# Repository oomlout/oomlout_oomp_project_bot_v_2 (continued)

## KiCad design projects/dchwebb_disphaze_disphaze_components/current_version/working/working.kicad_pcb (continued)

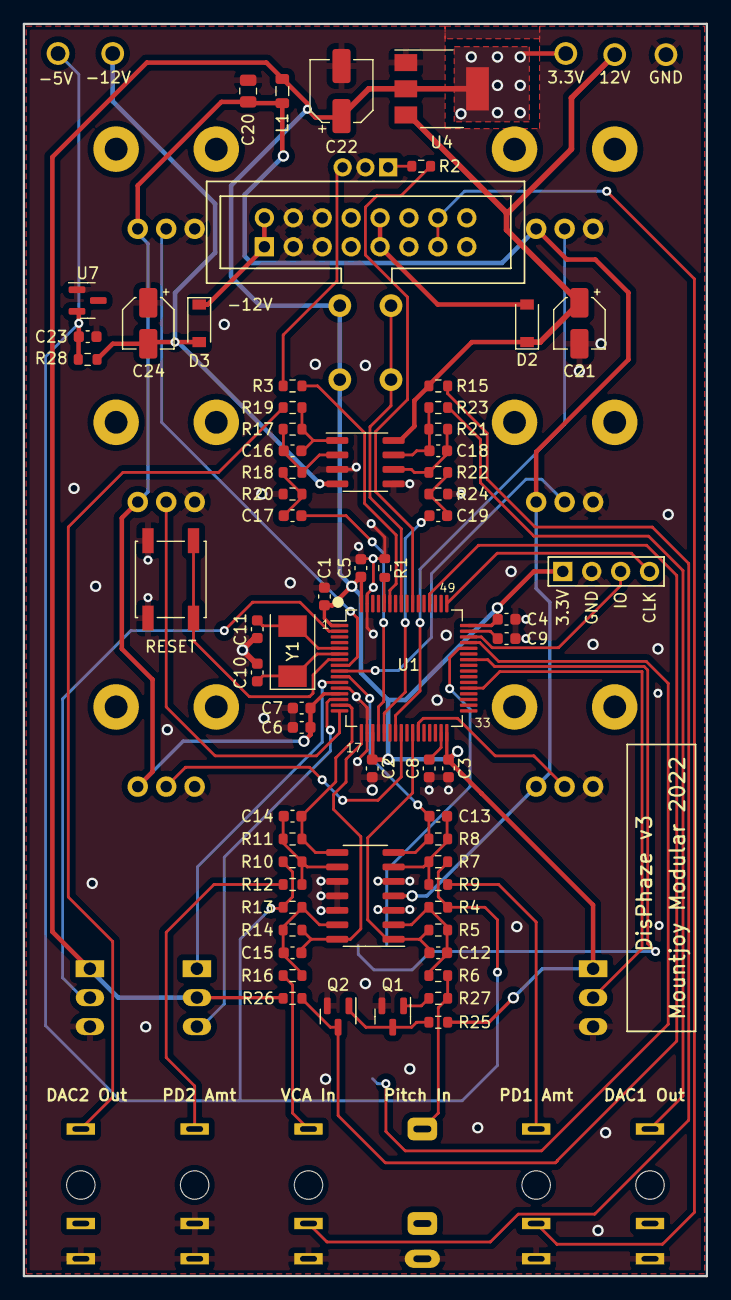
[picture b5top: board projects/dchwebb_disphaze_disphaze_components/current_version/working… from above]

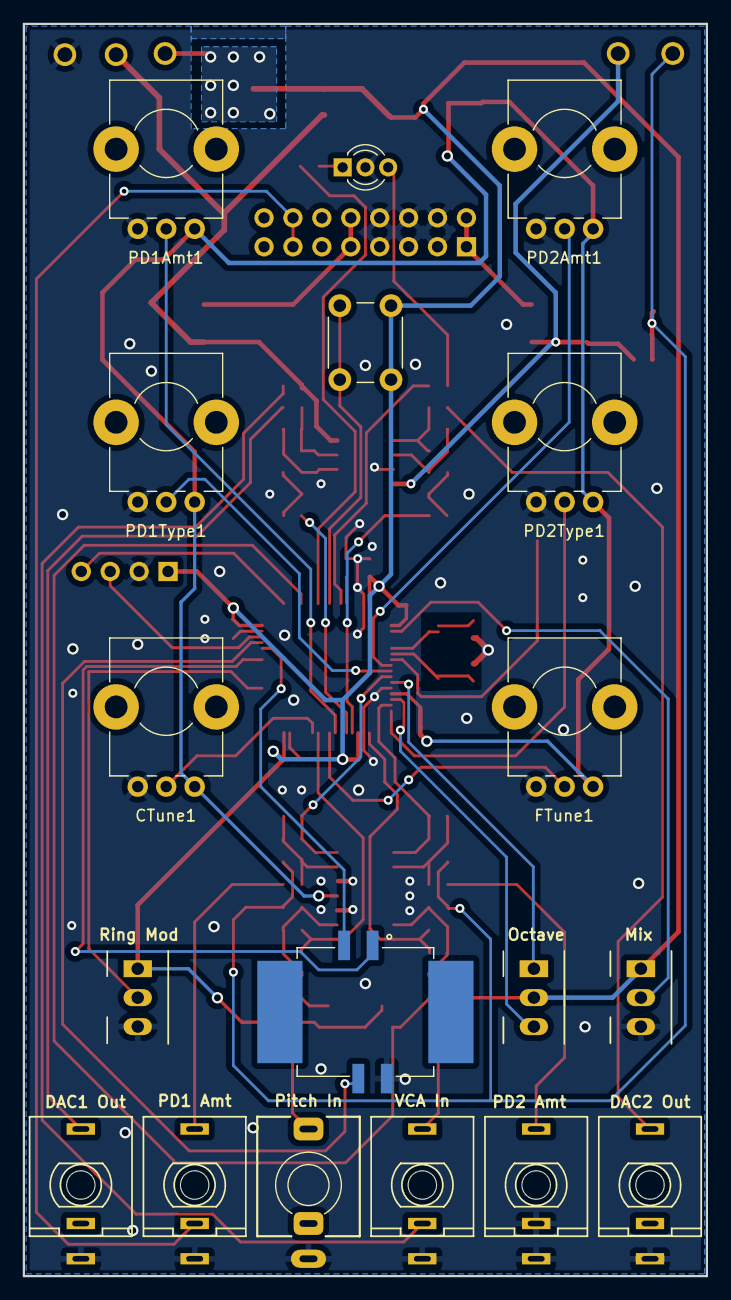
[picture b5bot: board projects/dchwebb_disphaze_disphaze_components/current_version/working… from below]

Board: 2 copper layers, 60.0 x 110.0 mm, 89 parts (18 on the bottom side), 61 nets.

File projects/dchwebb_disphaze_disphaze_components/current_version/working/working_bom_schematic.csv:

"Source:","C:\gh\oomlout_oomp_project_bot_v_2\projects\dchwebb_disphaze_disphaze_components\current_version\working\working.kicad_sch"
"Date:","30/09/2023 03:19:28"
"Tool:","Eeschema 7.0.6"
"Generator:","C:/Program Files/KiCad/7.0/bin/scripting/plugins/bom_csv_grouped_by_value_with_fp.py"
"Component Count:","89"
"Ref","Qnty","Value","Cmp name","Footprint","Description","Vendor","DNP"
"C1","1","4.7uF","C_Small","Capacitor_SMD:C_0603_1608Metric","Unpolarized capacitor, small symbol","",""
"C2, C3, C4, C5, C7, C23","6","100nF","C_Small","Capacitor_SMD:C_0603_1608Metric","Unpolarized capacitor, small symbol","",""
"C6","1","1uF","C_Small","Capacitor_SMD:C_0603_1608Metric","Unpolarized capacitor, small symbol","",""
"C8, C9","2","2.2uF","C_Small","Capacitor_SMD:C_0603_1608Metric","Unpolarized capacitor, small symbol","",""
"C10, C11","2","30pF","C_Small","Capacitor_SMD:C_0603_1608Metric","Unpolarized capacitor, small symbol","",""
"C12, C14","2","2.2nF","C_Small","Capacitor_SMD:C_0603_1608Metric","Unpolarized capacitor, small symbol","",""
"C13, C15","2","1.5nF","C_Small","Capacitor_SMD:C_0603_1608Metric","Unpolarized capacitor, small symbol","",""
"C16, C18","2","22pF","C_Small","Capacitor_SMD:C_0603_1608Metric","Unpolarized capacitor, small symbol","",""
"C17, C19","2","10uF","C_Small","Capacitor_SMD:C_0603_1608Metric","Unpolarized capacitor, small symbol","",""
"C20","1","10uF","C_Small","Capacitor_SMD:C_0805_2012Metric","Unpolarized capacitor, small symbol","",""
"C21, C24","2","22uF","C_Polarized_Small","Capacitor_SMD:CP_Elec_4x5.3","Polarized capacitor, small symbol","",""
"C22","1","47uF","C_Polarized_Small","Capacitor_SMD:CP_Elec_5x5.4","Polarized capacitor, small symbol","",""
"CTune1","1","B10k","R_Potentiometer","Custom_Footprints:Alpha_9mm_Potentiometer_Aligned","Potentiometer","",""
"D1","1","LED_Dual_AKA","LED_Dual_AKA","LED_THT:LED_D3.0mm-3","Dual LED, common cathode on pin 2","",""
"D2, D3","2","1N5819","1N5819","Diode_SMD:D_SOD-123","40V 1A Schottky Barrier Rectifier Diode, DO-41","",""
"FTune1","1","B10k","R_Potentiometer","Custom_Footprints:Alpha_9mm_Potentiometer_Aligned","Potentiometer","",""
"J1","1","SWD_Header","Conn_01x04_Male","Custom_Footprints:SWD_header","Generic connector, single row, 01x04, script generated (kicad-library-utils/schlib/autogen/connector/)","",""
"J2","1","USB_B_Micro","1734517-1","Custom_Footprints:USB_TE_1734517-1","","",""
"J3","1","PItch_In","AudioJack3","Custom_Footprints:Thonkiconn_Stereo-PJ366ST","Audio Jack, 3 Poles (Stereo / TRS)","",""
"J4","1","PD1_Amt_In","AudioJack2_Ground_Switch","Custom_Footprints:THONKICONN_hole","Audio Jack, 2 Poles (Mono / TS), Switched Pole (Normalling)","",""
"J5","1","PD2_Amt_In","AudioJack2_Ground_Switch","Custom_Footprints:THONKICONN_hole","Audio Jack, 2 Poles (Mono / TS), Switched Pole (Normalling)","",""
"J6","1","VCA_In","AudioJack2_Ground_Switch","Custom_Footprints:THONKICONN_hole","Audio Jack, 2 Poles (Mono / TS), Switched Pole (Normalling)","",""
"J7","1","DAC1_Out","AudioJack2_Ground_Switch","Custom_Footprints:THONKICONN_hole","Audio Jack, 2 Poles (Mono / TS), Switched Pole (Normalling)","",""
"J8","1","DAC2_Out","AudioJack2_Ground_Switch","Custom_Footprints:THONKICONN_hole","Audio Jack, 2 Poles (Mono / TS), Switched Pole (Normalling)","",""
"J9","1","Eurorack_16_pin_power","Eurorack_16_pin_power","Custom_Footprints:Eurorack_16_pin_header","","",""
"L1","1","L","L","Inductor_SMD:L_0805_2012Metric","Inductor","",""
"PD1Amt1","1","B10k","R_Potentiometer","Custom_Footprints:Alpha_9mm_Potentiometer_Aligned","Potentiometer","",""
"PD1Type1","1","B10k","R_Potentiometer","Custom_Footprints:Alpha_9mm_Potentiometer_Aligned","Potentiometer","",""
"PD2Amt1","1","B10k","R_Potentiometer","Custom_Footprints:Alpha_9mm_Potentiometer_Aligned","Potentiometer","",""
"PD2Type1","1","B10k","R_Potentiometer","Custom_Footprints:Alpha_9mm_Potentiometer_Aligned","Potentiometer","",""
"Q1, Q2","2","MMBT3904","MMBT3904","Package_TO_SOT_SMD:SOT-23","0.2A Ic, 40V Vce, Small Signal NPN Transistor, SOT-23","",""
"R1, R6, R9, R12, R16","5","100k","R_Small","Resistor_SMD:R_0603_1608Metric","Resistor, small symbol","",""
"R2, R3, R19, R23","4","1k","R_Small","Resistor_SMD:R_0603_1608Metric","Resistor, small symbol","",""
"R4","1","91k","R_Small","Resistor_SMD:R_0603_1608Metric","Resistor, small symbol","",""
"R5","1","56k","R_Small","Resistor_SMD:R_0603_1608Metric","Resistor, small symbol","",""
"R7","1","82k","R_Small","Resistor_SMD:R_0603_1608Metric","Resistor, small symbol","",""
"R8, R11, R14, R15, R20, R24","6","47k","R_Small","Resistor_SMD:R_0603_1608Metric","Resistor, small symbol","",""
"R10, R13, R17, R21","4","68k","R_Small","Resistor_SMD:R_0603_1608Metric","Resistor, small symbol","",""
"R18, R22","2","6.8k","R_Small","Resistor_SMD:R_0603_1608Metric","Resistor, small symbol","",""
"R25, R26, R27","3","4k7","R_Small","Resistor_SMD:R_0603_1608Metric","Resistor, small symbol","",""
"R28","1","2.2k","R_Small","Resistor_SMD:R_0603_1608Metric","Resistor, small symbol","",""
"RESET1","1","SW_Push","SW_Push","Custom_Footprints:SW_SPST_EVQQ2","Push button switch, generic, two pins","",""
"SW1","1","Octave_Switch","SW_SPDT_MSM","Custom_Footprints:SPDTSubMiniature","Switch, single pole double throw, center OFF position","",""
"SW2","1","DAC1_RingMod_Switch","SW_SPDT","Custom_Footprints:SPDTSubMiniature","Switch, single pole double throw","",""
"SW3","1","DAC2_Mix_Switch","SW_SPDT","Custom_Footprints:SPDTSubMiniature","Switch, single pole double throw","",""
"SW4","1","SW_Push","SW_Push","Custom_Footprints:SW_PUSH_6mm_aligned","Push button switch, generic, two pins","",""
"TP1, TP2, TP3, TP4, TP5","5","TestPoint","TestPoint","Custom_Footprints:1.3mm_Test_Point","test point","",""
"U1","1","STM32F405RGTx","STM32F405RGTx","Package_QFP:LQFP-64_10x10mm_P0.5mm","ARM Cortex-M4 MCU, 1024KB flash, 128KB RAM, 168MHz, 1.8-3.6V, 51 GPIO, LQFP-64","",""
"U2","1","TL072","TL072","Package_SO:SOIC-8_3.9x4.9mm_P1.27mm","Dual Low-Noise JFET-Input Operational Amplifiers, DIP-8/SOIC-8","",""
"U3","1","MCP6004","MCP6004","Package_SO:SOIC-14_3.9x8.7mm_P1.27mm","1MHz, Low-Power Op Amp, DIP-14/SOIC-14/TSSOP-14","",""
"U4","1","LM1117-3.3","LM1117-3.3","Package_TO_SOT_SMD:SOT-223-3_TabPin2","800mA Low-Dropout Linear Regulator, 3.3V fixed output, TO-220/TO-252/TO-263/SOT-223","",""
"U7","1","LM4040DBZ-5","LM4040DBZ-5","Package_TO_SOT_SMD:SOT-23","5.000V Precision Micropower Shunt Voltage Reference, SOT-23","",""
"Y1","1","12MHz_18pF","Crystal_Small","Crystal:Crystal_SMD_0603-2Pin_6.0x3.5mm","Two pin crystal, small symbol","",""

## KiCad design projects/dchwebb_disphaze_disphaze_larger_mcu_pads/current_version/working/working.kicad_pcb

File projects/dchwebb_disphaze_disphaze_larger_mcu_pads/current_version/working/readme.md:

# disphaze
 
## summary 
* id: dchwebb_disphaze_disphaze_larger_mcu_pads
* user: dchwebb
* name: disphaze
* board: disphaze_larger_mcu_pads
* repo: https://github.com/dchwebb/DisPhaze
* src_file_repo_kicad_pcb: Hardware/DisPhaze.kicad_pcb
* src_file_repo_kicad_pcb_link: https://github.com/dchwebb/DisPhaze/tree/master/Hardware/DisPhaze.kicad_pcb
* src_file_repo_kicad_sch: Hardware/DisPhaze.kicad_sch
* src_file_repo_kicad_sch_link: https://github.com/dchwebb/DisPhaze/tree/master/Hardware/DisPhaze.kicad_sch

* src_file_repo_sch: Hardware/DisPhaze.sch
* src_file_repo_sch_link: https://github.com/dchwebb/DisPhaze/tree/master/Hardware/DisPhaze.sch
* full details link: https://github.com/oomlout/oomlout_oomp_project_bot_v_2/tree/main/projects/dchwebb_disphaze_disphaze_larger_mcu_pads/current_version/working

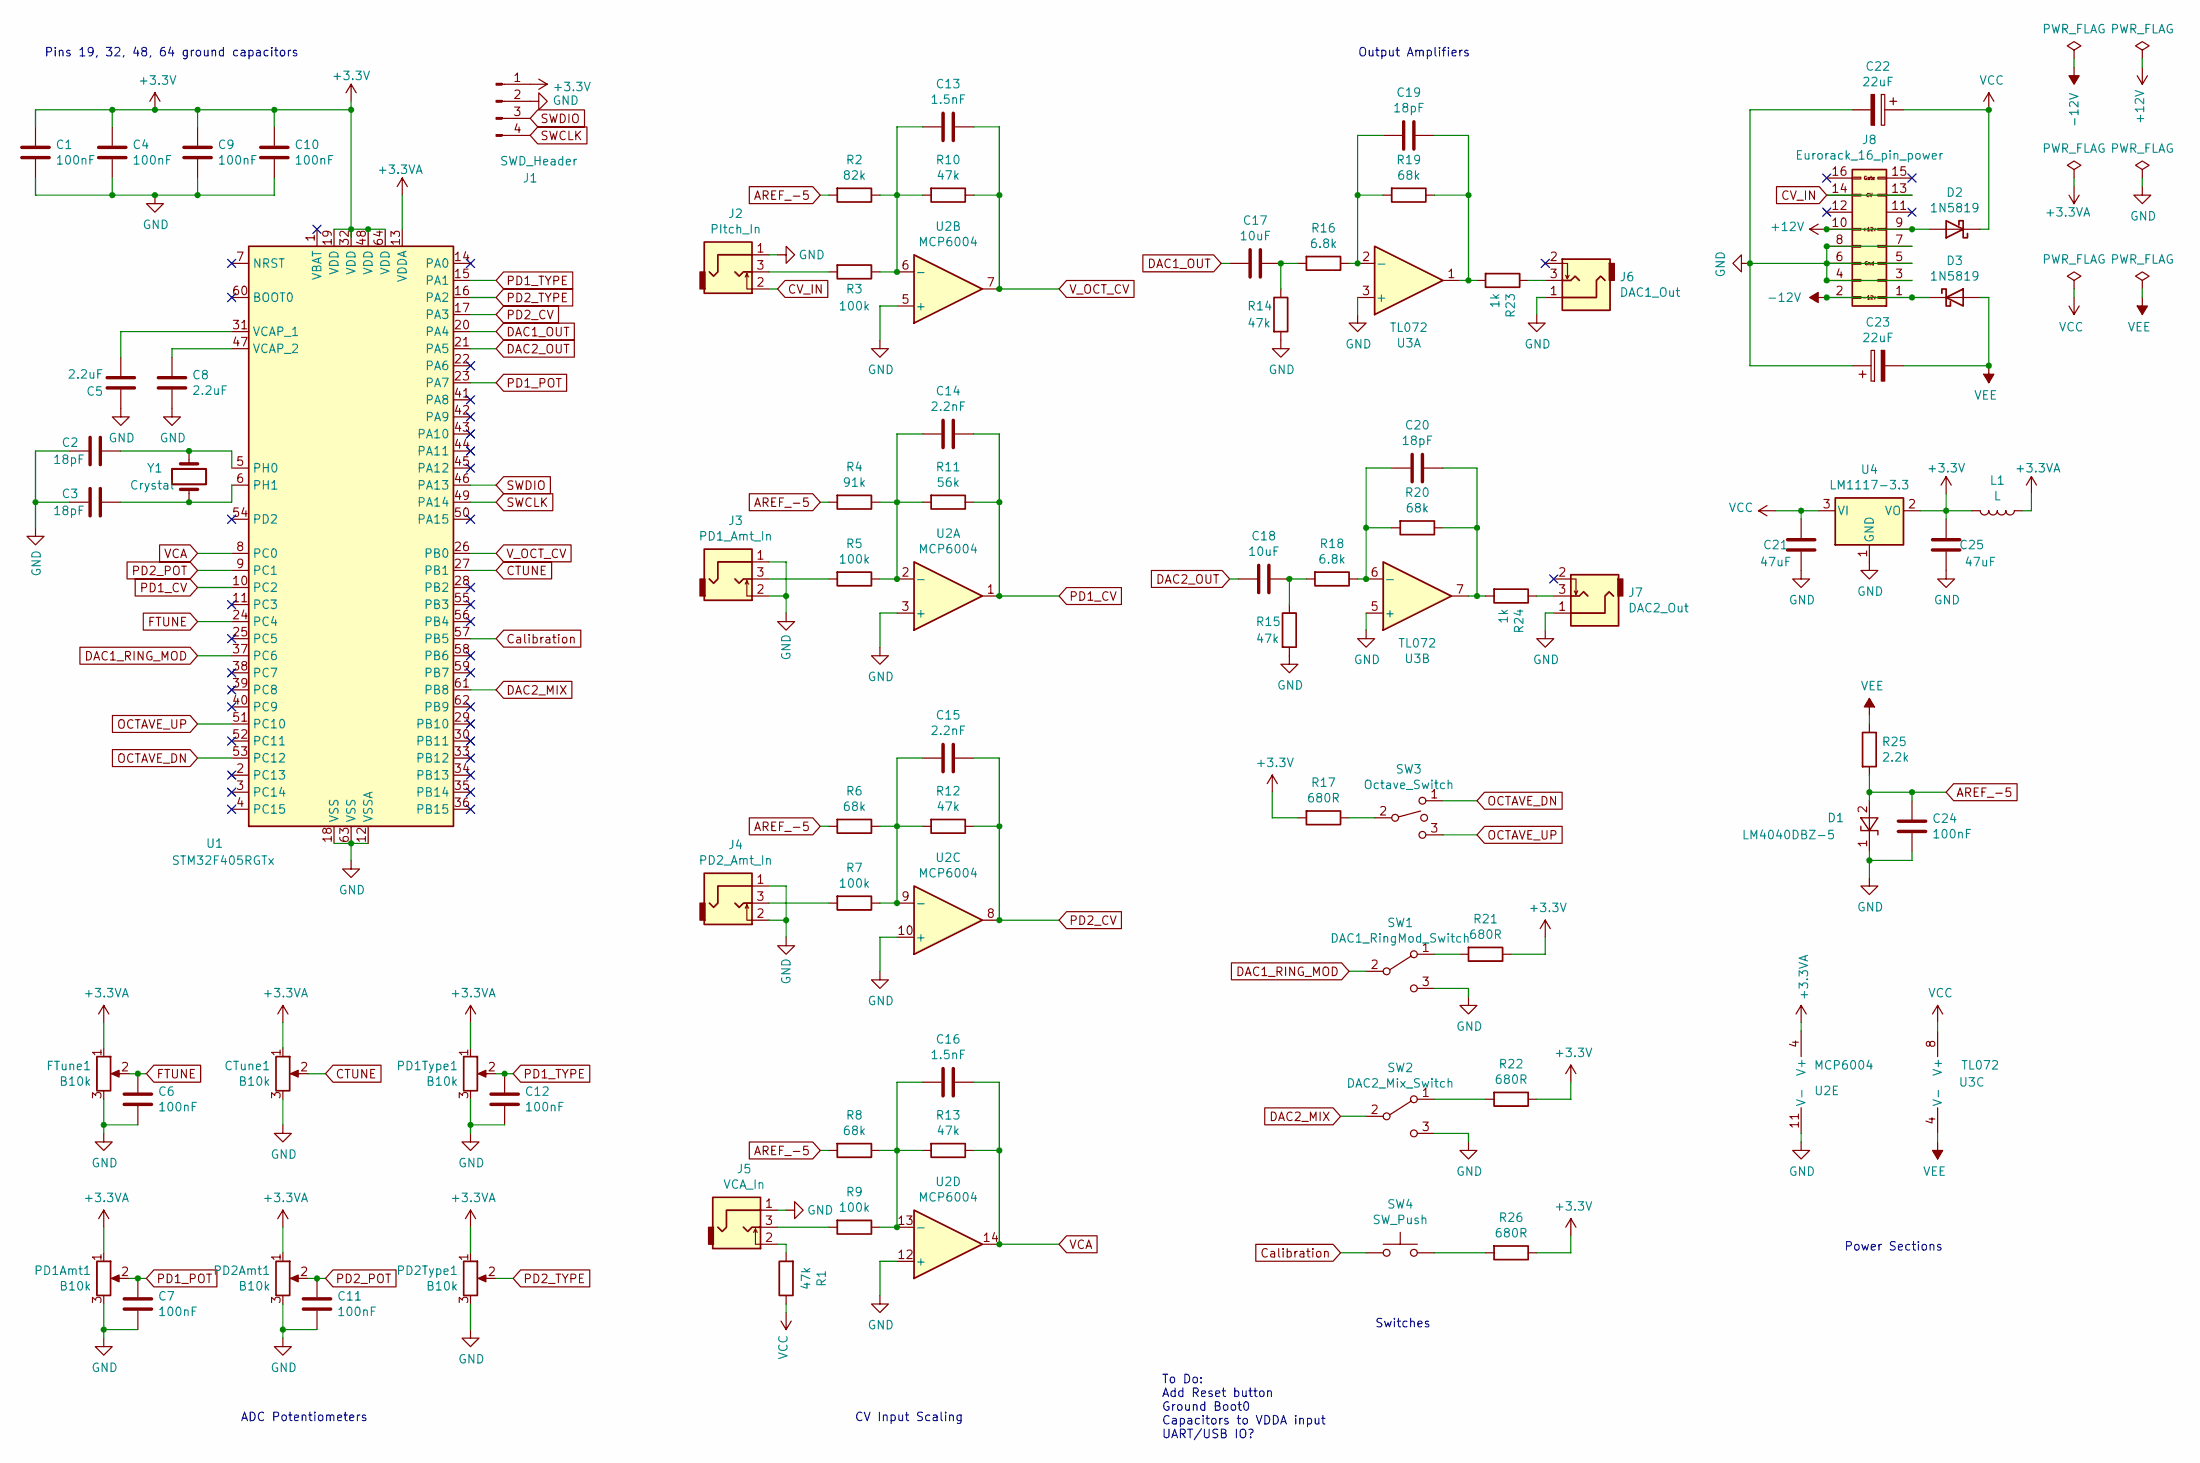
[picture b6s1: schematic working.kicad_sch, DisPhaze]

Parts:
C1, C4, C6, C7, C9, C10, C11, C12, C24: 100nF; C_0805_HandSoldering
C2, C3, C19, C20: 18pF; C_0805_HandSoldering
C5, C8: 2.2uF; C_0805_HandSoldering
C13, C16: 1.5nF; C_0805_HandSoldering
C14, C15: 2.2nF; C_0805_HandSoldering
C17, C18: 10uF; C_0805_HandSoldering
C21, C25: 47uF; CP_Elec_5x5.8
C22, C23: 22uF; CP_Elec_4x5.8
CTune1: B10k; Alpha_9mm_Potentiometer
D1: LM4040DBZ-5; SOT-23
D2, D3: 1N5819; D_SOD-123
FTune1: B10k; Alpha_9mm_Potentiometer
J1: SWD_Header; SWD_header
J2: PItch_In; THONKICONN_hole
J3: PD1_Amt_In; THONKICONN_hole
J4: PD2_Amt_In; THONKICONN_hole
J5: VCA_In; THONKICONN_hole
J6: DAC1_Out; THONKICONN_hole
J7: DAC2_Out; THONKICONN_hole
J8: Eurorack_16_pin_power; Eurorack_16_pin_header
L1: L; R_0805_HandSoldering
PD1Amt1, PD1Type1, PD2Amt1, PD2Type1: B10k; Alpha_9mm_Potentiometer
R1, R10, R12, R13, R14, R15: 47k; R_0805_HandSoldering
R2: 82k; R_0805_HandSoldering
R3, R5, R7, R9: 100k; R_0805_HandSoldering
R4: 91k; R_0805_HandSoldering
R6, R8, R19, R20: 68k; R_0805_HandSoldering
R11: 56k; R_0805_HandSoldering
R16, R18: 6.8k; R_0805_HandSoldering
R17, R21, R22, R26: 680R; R_0805_HandSoldering
R23, R24: 1k; R_0805_HandSoldering
R25: 2.2k; R_0805_HandSoldering
SW1: DAC1_RingMod_Switch; SPDTSubMiniature
SW2: DAC2_Mix_Switch; SPDTSubMiniature
SW3: Octave_Switch; SPDTSubMiniature
SW4: SW_Push; SW_SPST_EVQQ2
U1: STM32F405RGTx; LQFP-64_10x10mm_P0.5mm
U2: MCP6004; SOIC-14_N
U3: TL072; SOIC-8-N
U4: LM1117-3.3; TO-252-3_TabPin2
Y1: Crystal; Crystal_SMD

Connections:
+3.3VA: CTune1.1, FTune1.1, L1.1, PD1Amt1.1, PD1Type1.1, PD2Amt1.1, PD2Type1.1, U1.13 (VDDA), U2.4 (V+)
+3V3: C1.1, C4.1, C9.1, C10.1, C25.1, J1.1, L1.2, R17.2, R21.1, R22.1, R26.1, U1.19 (VDD), U1.32 (VDD), U1.48 (VDD), U1.64 (VDD), U4.2 (VO)
+12V: D2.2 (A), J8.9, J8.10
-12V: D3.1 (K), J8.1, J8.2
AREF_-5: C24.1, D1.2 (A), R2.2, R4.2, R6.2, R8.2, R25.2
CTUNE: CTune1.2, U1.27 (PB1)
CV_IN: J2.2, J8.13, J8.14
Calibration: SW4.1, U1.57 (PB5)
DAC1_OUT: C17.2, U1.20 (PA4)
DAC1_RING_MOD: SW1.2 (B), U1.37 (PC6); also elsewhere on the board
DAC2_MIX: SW2.2 (B), U1.61 (PB8)
DAC2_OUT: C18.2, U1.21 (PA5)
FTUNE: C6.1, FTune1.2, U1.24 (PC4)
GND: C1.2, C2.2, C3.2, C4.2, C5.1, C6.2, C7.2, C8.2, C9.2, C10.2, C11.2, C12.2, C21.2, C22.2, C23.1, C24.2, C25.2, CTune1.3, D1.1 (K), FTune1.3, J1.2, J2.1, J3.1, J3.2, J4.1, J4.2, J5.1, J6.1, J7.1, J8.3, J8.4, J8.5, J8.6, J8.7, J8.8, PD1Amt1.3, PD1Type1.3, PD2Amt1.3, PD2Type1.3, R14.2, R15.2, SW1.3 (C), SW2.3 (C), U1.12 (VSSA), U1.18 (VSS), U1.63 (VSS), U2.3 (+), U2.5 (+), U2.10 (+), U2.11 (V-), U2.12 (+), U3.3 (+), U3.5 (+), U4.1 (GND); also elsewhere on the board
unnamed: C2.1, U1.5 (PH0), Y1.2
unnamed: C3.1, U1.6 (PH1), Y1.1
unnamed: C5.2, U1.31 (VCAP_1)
unnamed: C8.1, U1.47 (VCAP_2)
unnamed: C13.1, R2.1, R3.1, R10.2, U2.6 (-)
unnamed: C14.1, R4.1, R5.1, R11.2, U2.2 (-)
unnamed: C15.1, R6.1, R7.1, R12.2, U2.9 (-)
unnamed: C16.1, R8.1, R9.1, R13.2, U2.13 (-)
unnamed: C17.1, R14.1, R16.2
unnamed: C18.1, R15.1, R18.2
unnamed: C19.1, R16.1, R19.2, U3.2 (-)
unnamed: C19.2, R19.1, R23.2, U3.1
unnamed: C20.1, R18.1, R20.2, U3.6 (-)
unnamed: C20.2, R20.1, R24.2, U3.7
unnamed: J2.3, R3.2
unnamed: J3.3, R5.2
unnamed: J4.3, R7.2
unnamed: J5.2, R1.2
unnamed: J5.3, R9.2
unnamed: J6.3, R23.1
unnamed: J7.3, R24.1
unnamed: R17.1, SW3.2
unnamed 42: R21.2, SW1.1 (A); also elsewhere on the board
unnamed: R22.2, SW2.1 (A)
unnamed: R26.2, SW4.2
OCTAVE_DN: SW3.1, U1.53 (PC12)
OCTAVE_UP: SW3.3, U1.51 (PC10)
PD1_CV: C14.2, R11.1, U1.10 (PC2), U2.1
PD1_POT: C7.1, PD1Amt1.2, U1.23 (PA7)
PD1_TYPE: C12.1, PD1Type1.2, U1.15 (PA1)
PD2_CV: C15.2, R12.1, U1.17 (PA3), U2.8
PD2_POT: C11.1, PD2Amt1.2, U1.9 (PC1)
PD2_TYPE: PD2Type1.2, U1.16 (PA2)
SWCLK: J1.4, U1.49 (PA14)
SWDIO: J1.3, U1.46 (PA13)
VCA: C16.2, R13.1, U1.8 (PC0), U2.14
VCC: C21.1, C22.1, D2.1 (K), R1.1, U3.8 (V+), U4.3 (VI)
VEE: C23.2, D3.2 (A), R25.1, U3.4 (V-)
V_OCT_CV: C13.2, R10.1, U1.26 (PB0), U2.7

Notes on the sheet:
To Do: Add Reset button Ground Boot0 Capacitors to VDDA input UART/USB IO?
Output Amplifiers
Switches
Pins 19, 32, 48, 64 ground capacitors
Power Sections
ADC Potentiometers
CV Input Scaling

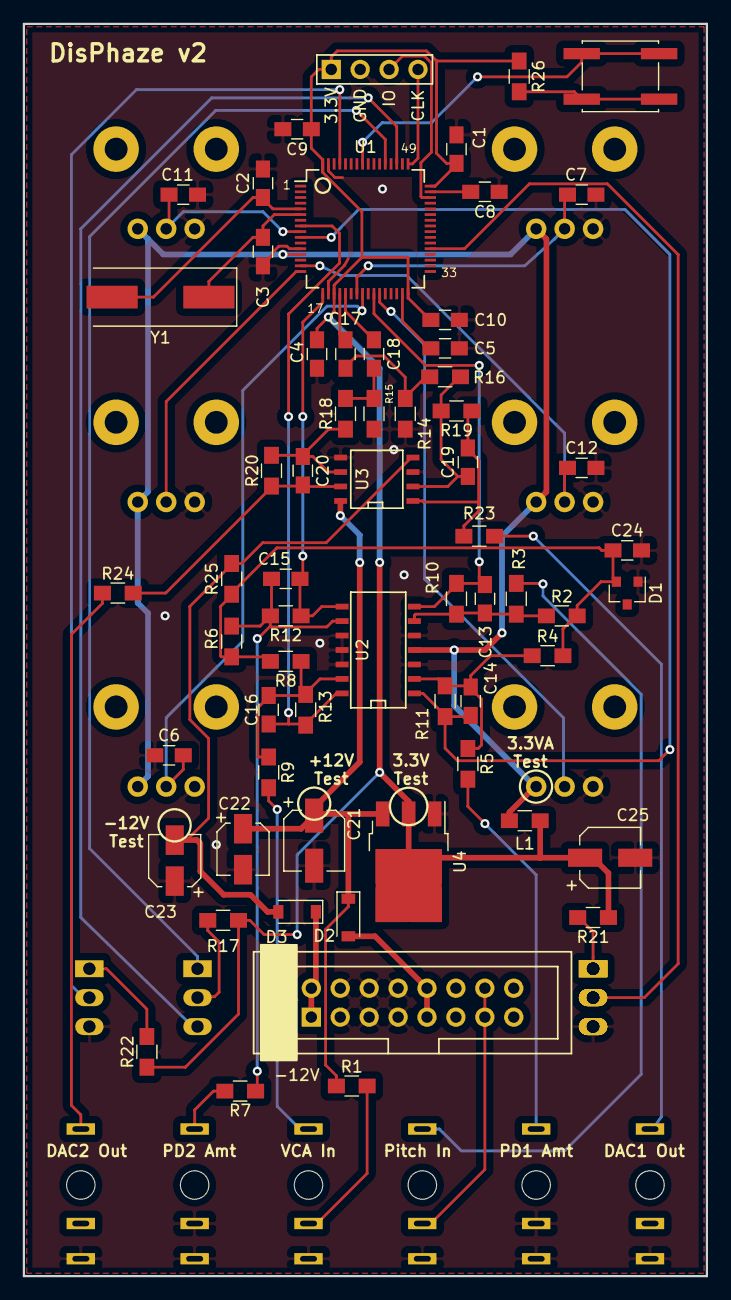
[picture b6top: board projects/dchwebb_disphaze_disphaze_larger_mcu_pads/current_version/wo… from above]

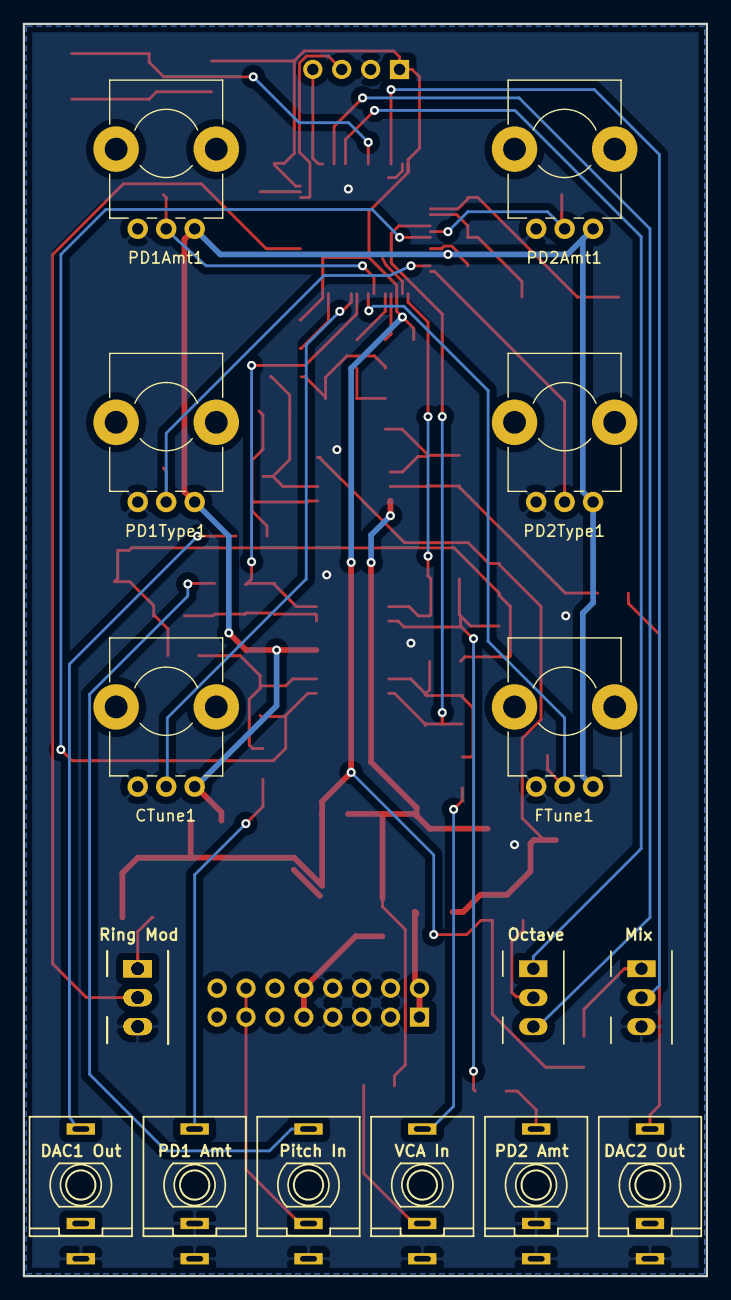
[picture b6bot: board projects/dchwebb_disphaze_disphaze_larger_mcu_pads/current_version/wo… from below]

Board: 2 copper layers, 60.0 x 110.0 mm, 80 parts (17 on the bottom side), 53 nets.

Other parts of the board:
SW1#2, SW1#3: DAC1_RingMod_Switch; SPDTSubMiniature

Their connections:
DAC1_RING_MOD: SW1#2.2, SW1#3.2; also elsewhere on the board
GND: SW1#2.3, SW1#3.3; also elsewhere on the board
unnamed 42: SW1#2.1, SW1#3.1; also elsewhere on the board

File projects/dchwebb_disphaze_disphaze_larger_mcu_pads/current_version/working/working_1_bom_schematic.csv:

"Source:","C:\gh\oomlout_oomp_project_bot_v_2\projects\dchwebb_disphaze_disphaze_larger_mcu_pads\current_version\working\working_1.kicad_sch"
"Date:","30/09/2023 03:29:46"
"Tool:","Eeschema 7.0.6"
"Generator:","C:/Program Files/KiCad/7.0/bin/scripting/plugins/bom_csv_grouped_by_value_with_fp.py"
"Component Count:","78"
"Ref","Qnty","Value","Cmp name","Footprint","Description","Vendor","DNP"
"C1, C4, C6, C7, C9, C10, C11, C12, C24","9","100nF","C","Capacitors_SMD:C_0805_HandSoldering","Unpolarized capacitor","",""
"C2, C3, C19, C20","4","18pF","C","Capacitors_SMD:C_0805_HandSoldering","Unpolarized capacitor","",""
"C5, C8","2","2.2uF","C","Capacitors_SMD:C_0805_HandSoldering","Unpolarized capacitor","",""
"C13, C16","2","1.5nF","C","Capacitors_SMD:C_0805_HandSoldering","Unpolarized capacitor","",""
"C14, C15","2","2.2nF","C","Capacitors_SMD:C_0805_HandSoldering","Unpolarized capacitor","",""
"C17, C18","2","10uF","C","Capacitors_SMD:C_0805_HandSoldering","Unpolarized capacitor","",""
"C21, C25","2","47uF","C","Capacitors_SMD:CP_Elec_5x5.8","Unpolarized capacitor","",""
"C22, C23","2","22uF","CP","Capacitors_SMD:CP_Elec_4x5.8","","",""
"CTune1","1","B10k","R_POT","Custom_Footprints:Alpha_9mm_Potentiometer","","",""
"D1","1","LM4040DBZ-5","LM4040DBZ-10","TO_SOT_Packages_SMD:SOT-23","10.00V Precision Micropower Shunt Voltage Reference, SOT-23","",""
"D2, D3","2","1N5819","1N5819","Diodes_SMD:D_SOD-123","40V 1A Schottky Barrier Rectifier Diode, DO-41","",""
"FTune1","1","B10k","R_POT","Custom_Footprints:Alpha_9mm_Potentiometer","","",""
"J1","1","SWD_Header","Conn_01x04_Male","Custom_Footprints:SWD_header","Generic connector, single row, 01x04, script generated (kicad-library-utils/schlib/autogen/connector/)","",""
"J2","1","PItch_In","AudioJack2_Ground_Switch","Custom_Footprints:THONKICONN_hole","Audio Jack, 2 Poles (Mono / TS), Switched Pole (Normalling)","",""
"J3","1","PD1_Amt_In","AudioJack2_Ground_Switch","Custom_Footprints:THONKICONN_hole","Audio Jack, 2 Poles (Mono / TS), Switched Pole (Normalling)","",""
"J4","1","PD2_Amt_In","AudioJack2_Ground_Switch","Custom_Footprints:THONKICONN_hole","Audio Jack, 2 Poles (Mono / TS), Switched Pole (Normalling)","",""
"J5","1","VCA_In","AudioJack2_Ground_Switch","Custom_Footprints:THONKICONN_hole","Audio Jack, 2 Poles (Mono / TS), Switched Pole (Normalling)","",""
"J6","1","DAC1_Out","AudioJack2_Ground_Switch","Custom_Footprints:THONKICONN_hole","Audio Jack, 2 Poles (Mono / TS), Switched Pole (Normalling)","",""
"J7","1","DAC2_Out","AudioJack2_Ground_Switch","Custom_Footprints:THONKICONN_hole","Audio Jack, 2 Poles (Mono / TS), Switched Pole (Normalling)","",""
"J8","1","Eurorack_16_pin_power","Eurorack_16_pin_power","Custom_Footprints:Eurorack_16_pin_header","","",""
"L1","1","L","L","Resistors_SMD:R_0805_HandSoldering","Inductor","",""
"PD1Amt1","1","B10k","R_POT","Custom_Footprints:Alpha_9mm_Potentiometer","","",""
"PD1Type1","1","B10k","R_POT","Custom_Footprints:Alpha_9mm_Potentiometer","","",""
"PD2Amt1","1","B10k","R_POT","Custom_Footprints:Alpha_9mm_Potentiometer","","",""
"PD2Type1","1","B10k","R_POT","Custom_Footprints:Alpha_9mm_Potentiometer","","",""
"R1, R10, R12, R13, R14, R15","6","47k","R","Resistors_SMD:R_0805_HandSoldering","Resistor","",""
"R2","1","82k","R","Resistors_SMD:R_0805_HandSoldering","Resistor","",""
"R3, R5, R7, R9","4","100k","R","Resistors_SMD:R_0805_HandSoldering","Resistor","",""
"R4","1","91k","R","Resistors_SMD:R_0805_HandSoldering","Resistor","",""
"R6, R8, R19, R20","4","68k","R","Resistors_SMD:R_0805_HandSoldering","Resistor","",""
"R11","1","56k","R","Resistors_SMD:R_0805_HandSoldering","Resistor","",""
"R16, R18","2","6.8k","R","Resistors_SMD:R_0805_HandSoldering","Resistor","",""
"R17, R21, R22, R26","4","680R","R","Resistors_SMD:R_0805_HandSoldering","Resistor","",""
"R23, R24","2","1k","R","Resistors_SMD:R_0805_HandSoldering","Resistor","",""
"R25","1","2.2k","R","Resistors_SMD:R_0805_HandSoldering","Resistor","",""
"SW1","1","DAC1_RingMod_Switch","SW_SPDT","Custom_Footprints:SPDTSubMiniature","Switch, single pole double throw","",""
"SW2","1","DAC2_Mix_Switch","SW_SPDT","Custom_Footprints:SPDTSubMiniature","Switch, single pole double throw","",""
"SW3","1","Octave_Switch","SW_SPDT_MSM","Custom_Footprints:SPDTSubMiniature","Switch, single pole double throw, center OFF position","",""
"SW4","1","SW_Push","SW_Push","Custom_Footprints:SW_SPST_EVQQ2","Push button switch, generic, two pins","",""
"U1","1","STM32F405RGTx","STM32F405RGTx","Package_QFP:LQFP-64_10x10mm_P0.5mm","ARM Cortex-M4 MCU, 1024KB flash, 128KB RAM, 168MHz, 1.8-3.6V, 51 GPIO, LQFP-64","",""
"U2","1","MCP6004","MCP6004","SMD_Packages:SOIC-14_N","1MHz, Low-Power Op Amp, DIP-14/SOIC-14/TSSOP-14","",""
"U3","1","TL072","TL072","SMD_Packages:SOIC-8-N","Dual Low-Noise JFET-Input Operational Amplifiers, DIP-8/SOIC-8","",""
"U4","1","LM1117-3.3","LM1117-3.3","TO_SOT_Packages_SMD:TO-252-3_TabPin2","800mA Low-Dropout Linear Regulator, 3.3V fixed output, TO-220/TO-252/TO-263/SOT-223","",""
"Y1","1","Crystal","Crystal","Custom_Footprints:Crystal_SMD","Two pin crystal","",""
